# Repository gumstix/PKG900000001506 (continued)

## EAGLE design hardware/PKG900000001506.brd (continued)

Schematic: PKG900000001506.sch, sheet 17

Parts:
U1: WS2812B-Mini-V3; WS2812B-MINI

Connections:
3.5.0V_VCC_5.0: U1.1 (VDD); also elsewhere on the board
15.PWM0_PWM: U1.4 (DIN); also elsewhere on the board
19.DATA_OUT_DATA: U1.2 (DOUT); also elsewhere on the board
GND: U1.3 (VSS); also elsewhere on the board

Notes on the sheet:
Top-side RGB LED (3535)

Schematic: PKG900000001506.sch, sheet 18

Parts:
C1: 47pF; 0201
D1: B72590D50A060; D0402
R1: 10K 1%; 0201
R2: 150R; 0201
S1: EVQ

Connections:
15.GPIO6_GPIO: C1.1, R2.2; also elsewhere on the board
15.VLOGIC_VLOGIC: R1.2; also elsewhere on the board
BTN_A$20: D1.P2, R1.1, R2.1, S1.B@2 (B')
GND: C1.2, D1.P1, S1.A@1 (A); also elsewhere on the board

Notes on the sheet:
Pushbutton

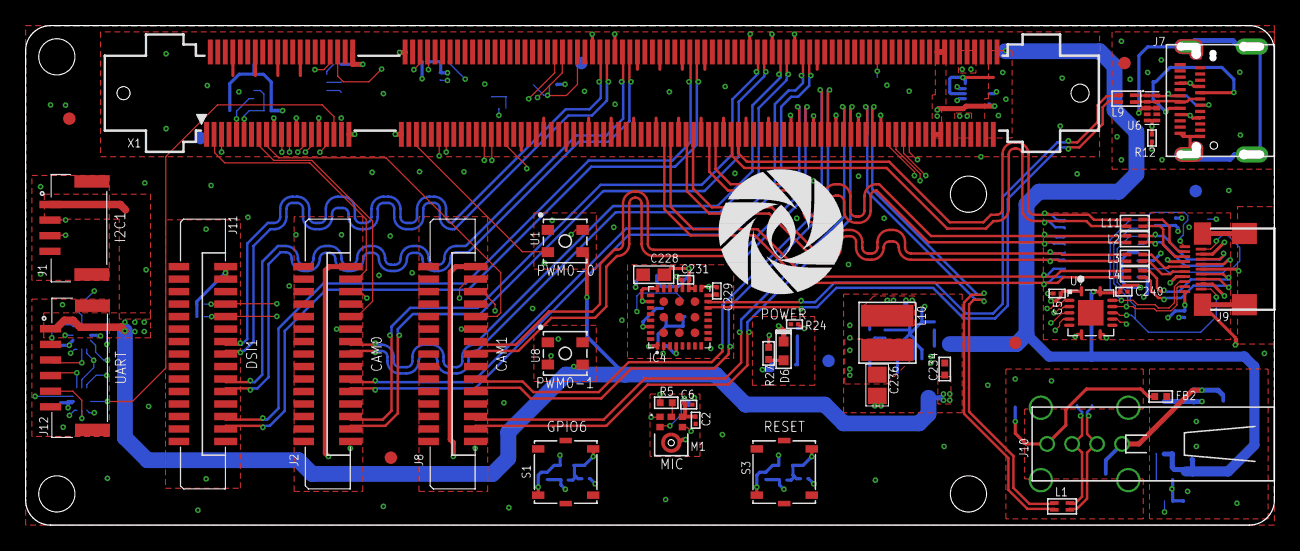
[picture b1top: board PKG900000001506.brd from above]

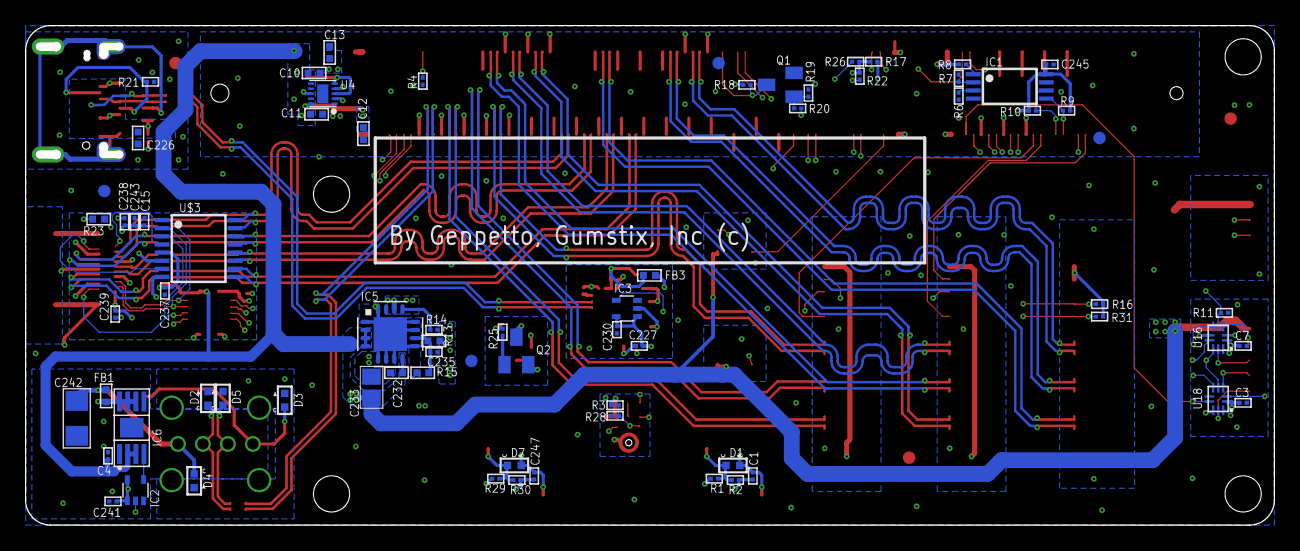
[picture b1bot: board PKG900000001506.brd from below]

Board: 6 copper layers, 100.0 x 40.0 mm, 122 parts (74 on the bottom side), 116 nets.

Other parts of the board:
U$1, U$41, U$43, U$45: DNP; GEPPETTO_HOLE_2.9

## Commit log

2020-10-13 Add README content, spec sheet and folders
2020-10-15 Added hardware documents for revision 2.
2020-10-15 add links to brd and sch
2020-10-19 Add demo links and data.
2020-10-19 Update firmware image to Ubuntu 20.04 CM4 image.
2020-11-23 Update firmware.md
    Add image username and password information.
2021-07-13 ROS2 server initial commit
2021-07-13 ROS2 folder update
